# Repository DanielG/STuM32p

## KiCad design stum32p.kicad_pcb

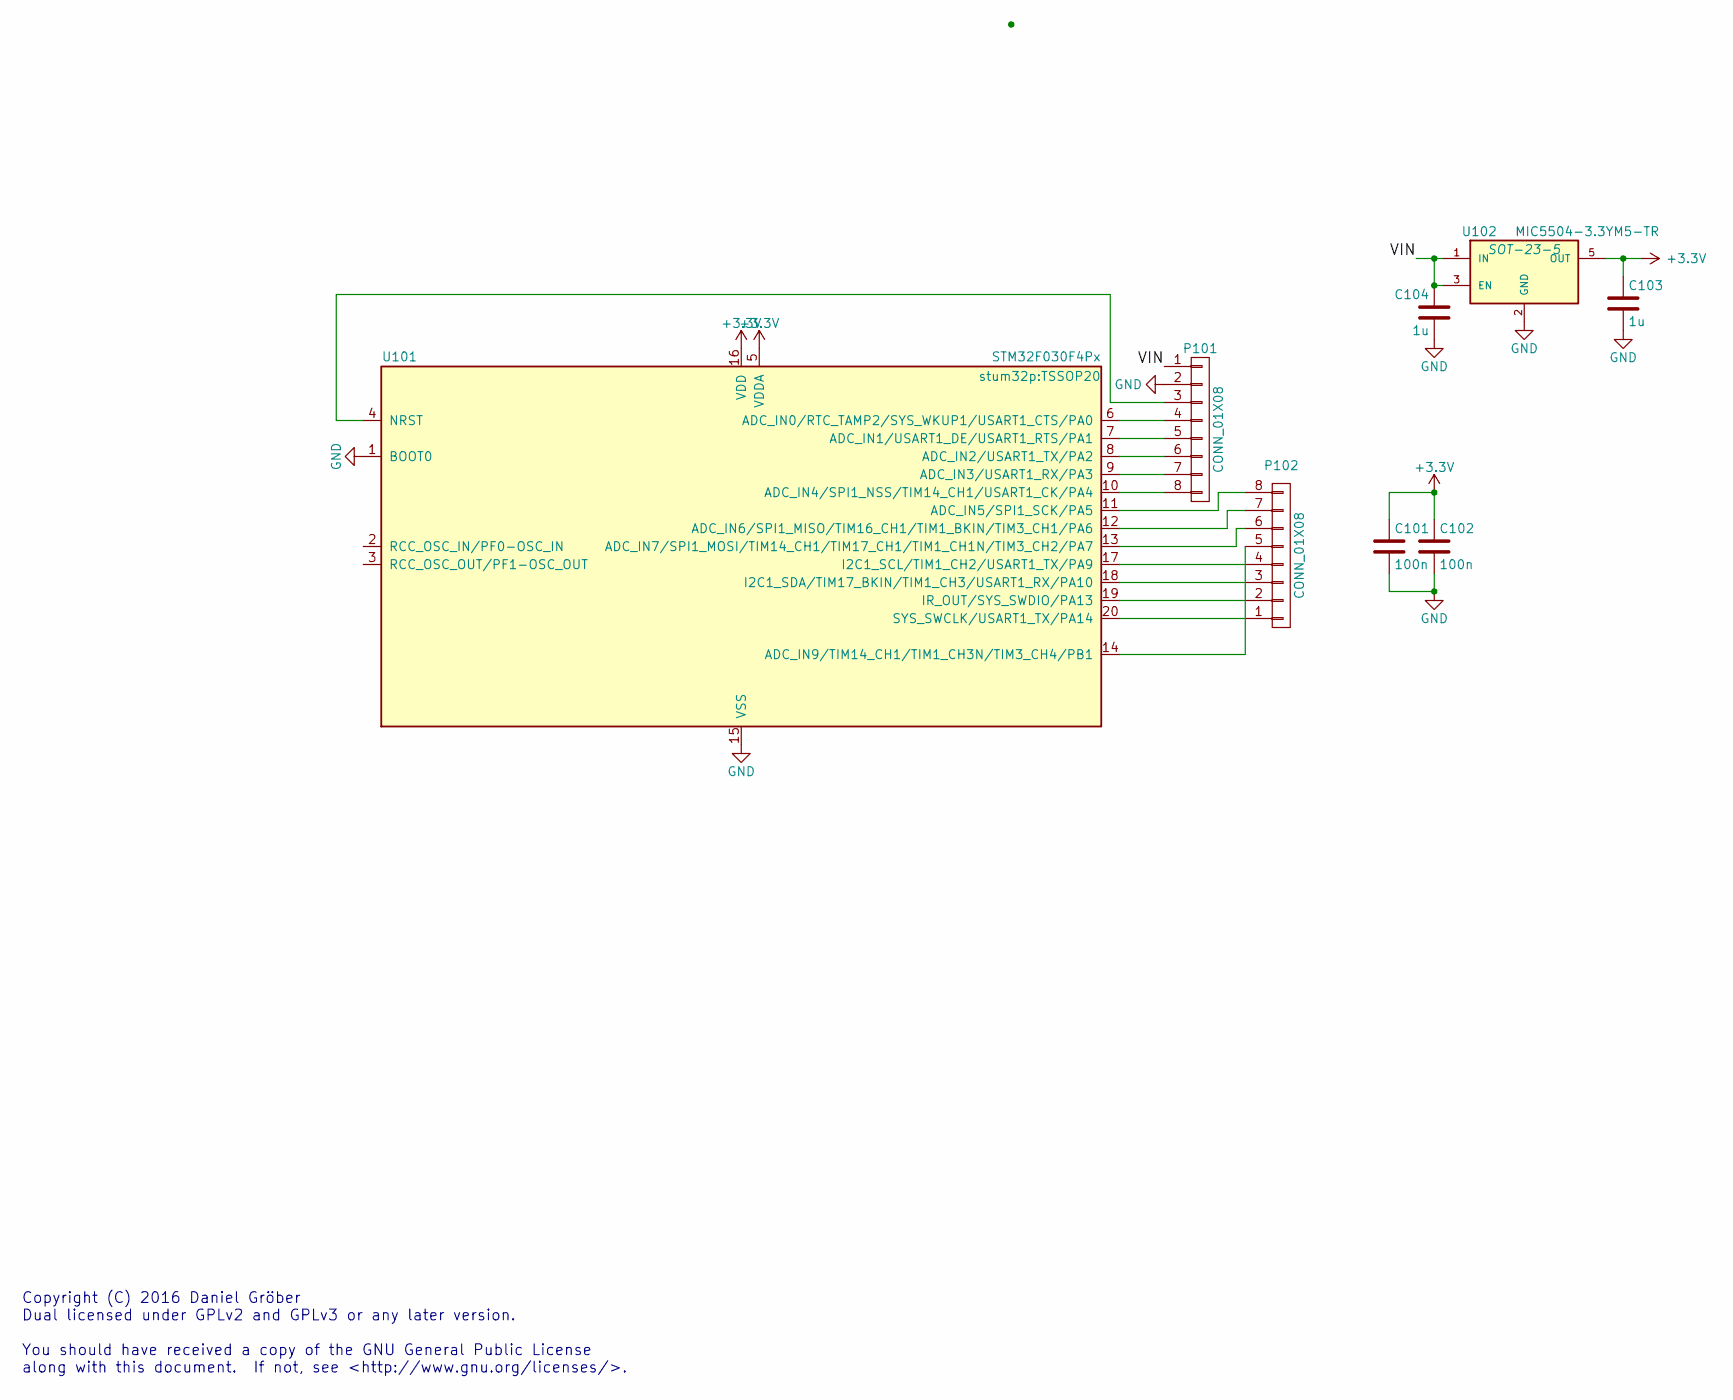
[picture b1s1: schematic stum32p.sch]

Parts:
C101, C102: 100n; C_0603
C103, C104: 1u; C_0603
P101, P102: CONN_01X08; Pin_Header_Straight_1x08
U101: STM32F030F4Px; TSSOP20
U102: MIC5504-3.3YM5-TR; SOT-23-5

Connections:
+3V3: C101.1, C102.1, C103.1, U101.5 (VDDA), U101.16 (VDD), U102.5 (OUT)
/VIN: C104.1, P101.1, U102.1 (IN), U102.3 (EN)
GND: C101.2, C102.2, C103.2, C104.2, P101.2, U101.1 (BOOT0), U101.15 (VSS), U102.2 (GND)
unnamed: P101.3, U101.4 (NRST)
unnamed: P101.4, U101.6 (ADC_IN0/RTC_TAMP2/SYS_WKUP1/USART1_CTS/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)
unnamed: P101.5, U101.7 (ADC_IN1/USART1_DE/USART1_RTS/PA1)
unnamed: P101.6, U101.8 (ADC_IN2/USART1_TX/PA2)
unnamed: P101.7, U101.9 (ADC_IN3/USART1_RX/PA3)
unnamed: P101.8, U101.10 (ADC_IN4/SPI1_NSS/TIM14_CH1/USART1_CK/PA4)
unnamed: P102.1, U101.20 (SYS_SWCLK/USART1_TX/PA14)
unnamed: P102.2, U101.19 (IR_OUT/SYS_SWDIO/PA13)
unnamed: P102.3, U101.18 (I2C1_SDA/TIM17_BKIN/TIM1_CH3/USART1_RX/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)
unnamed: P102.4, U101.17 (I2C1_SCL/TIM1_CH2/USART1_TX/PA9)
unnamed: P102.5, U101.14 (ADC_IN9/TIM14_CH1/TIM1_CH3N/TIM3_CH4/PB1)
unnamed: P102.6, U101.13 (ADC_IN7/SPI1_MOSI/TIM14_CH1/TIM17_CH1/T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)
unnamed: P102.7, U101.12 (ADC_IN6/SPI1_MISO/TIM16_CH1/TIM1_BKIN/T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)
unnamed: P102.8, U101.11 (ADC_IN5/SPI1_SCK/PA5)

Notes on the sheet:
Copyright (C) 2016 Daniel Gröber Dual licensed under GPLv2 and GPLv3 or any later version. You should have received a copy of the GNU General Public License along with this document. If not, see <http://www.gnu.org/licenses/>.

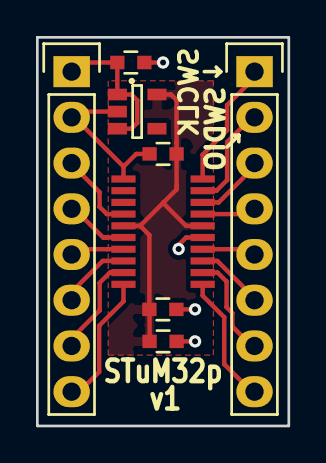
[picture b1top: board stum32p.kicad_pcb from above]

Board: 2 copper layers, 14.0 x 21.6 mm, 8 parts (0 on the bottom side), 17 nets.

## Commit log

2016-07-08 branch created
2016-07-08 Initial
2016-07-09 docs
